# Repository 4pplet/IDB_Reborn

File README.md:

# IDB_reborn
Reborn of the PCB for the IDB60

Made in KiCad Nightly

Originally designed by pngu.
Redigned by Mattelec.

Tested via private GB of the PCB. Might need some filing though.

Any question refer to Mattelec#9468 at Discord

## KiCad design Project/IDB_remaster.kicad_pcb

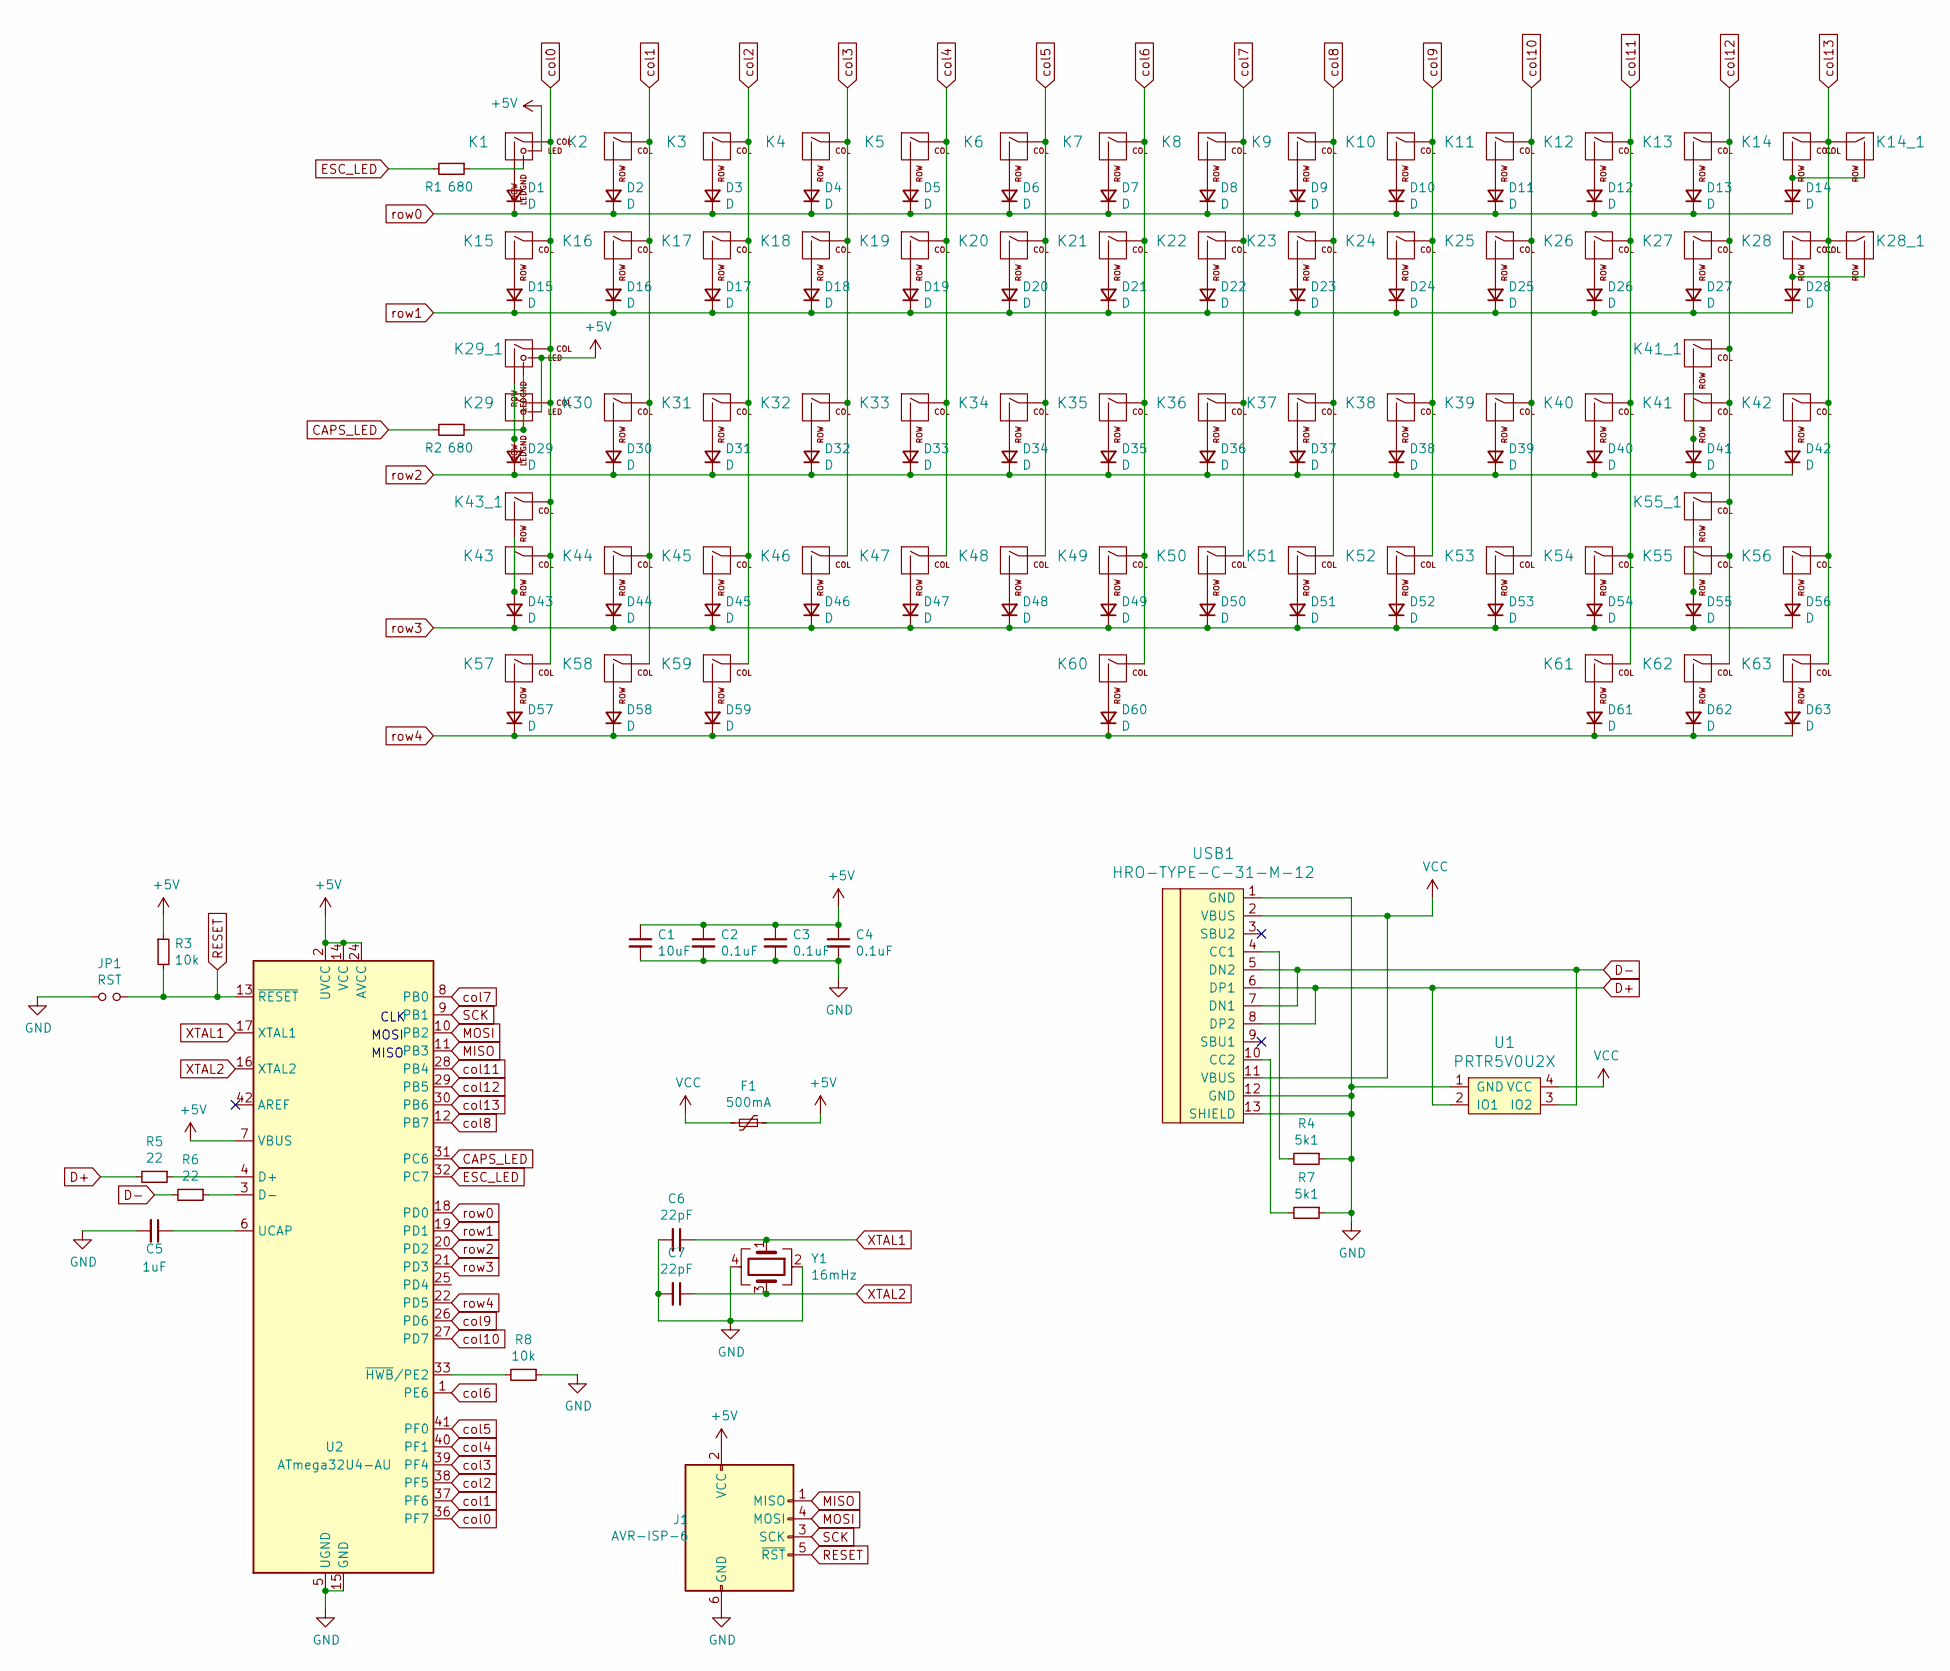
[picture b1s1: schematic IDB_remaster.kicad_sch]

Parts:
C1: 10uF; C_0805_2012Metric; LCSC C15850
C2, C3, C4: 0.1uF; C_0805_2012Metric; LCSC C49678
C5: 1uF; C_0805_2012Metric; LCSC C28323
C6, C7: 22pF; C_0805_2012Metric; LCSC C1804
D1, D2, D3, D4, D5, D6, D7, D8, D9, D10, D11, D12, D13, D14, D15, D16, D17, D18, D19, D20, D21, D22, D23, D24, D25, D26, D27, D28, D29, D30, D31, D32, D33, D34, D35, D36, D37, D38, D39, D40, D41, D42, D43, D44, D45, D46, D47, D48, D49, D50, D51, D52, D53, D54, D55, D56, D57, D58, D59, D60, D61, D62, D63: D; D_SOD-123-Pretty; LCSC C64898
F1: 500mA; Fuse_1206_3216Metric; LCSC C70076
J1: AVR-ISP-6; Reset_Pretty-Mask
JP1: RST; Reset_holes
K1: MXOnly-1U-19mm
K2, K3, K4, K5, K6, K7, K8, K9, K10, K11, K12, K13, K14_1, K16, K17, K18, K19, K20, K21, K22, K23, K24, K25, K26, K27, K30, K31, K32, K33, K34, K35, K36, K37, K38, K39, K40, K41, K42, K44, K45, K46, K47, K48, K49, K50, K51, K52, K53, K54, K56, K58, K62: MXOnly-1U-NoLED-19mm
K14: MXOnly-2U-NoLED-19mm
K15, K28, K57, K59, K61, K63: MXOnly-1.5U--NoLED19mm
K28_1: MXOnly-ISO-ROTATED-NoLED-19mm
K29: MXOnly-1.75U-19mm
K29_1: MXOnly-1.25U-ReverseLED19mm
K41_1, K43_1: MXOnly-2.25U-NoLED-19mm
K43: MXOnly-1.25U-NoLED-19mm
K55: MXOnly-1.75U-NoLED-19mm
K55_1: MXOnly-2.75U-NoLED-19mm
K60: MXOnly-7U-ReversedStabilizers-NoLED-19mm
R1, R2: 680; R_0805_2012Metric; LCSC C25324
R3, R8: 10k; R_0805_2012Metric; LCSC C17414
R4, R7: 5k1; R_0805_2012Metric; LCSC C118848
R5, R6: 22; R_0805_2012Metric; LCSC C416086
U1: PRTR5V0U2X; SOT143B; LCSC C78442
U2: ATmega32U4-AU; TQFP-44_10x10mm_P0.8mm; LCSC C44854
USB1: HRO-TYPE-C-31-M-12; HRO-TYPE-C-31-M-12-Assembly; LCSC C165948
Y1: 16mHz; Crystal_SMD_3225-4Pin_3.2x2.5mm; LCSC C13738

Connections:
+5V: C1.1, C2.1, C3.1, C4.1, F1.1, J1.2 (VCC), K1.3 (LED), K29.3 (LED), K29_1.3 (LED), R3.1, U2.2 (UVCC), U2.7 (VBUS), U2.14 (VCC), U2.24 (AVCC), U2.34 (VCC), U2.44 (AVCC)
CAPS_LED: R2.2, U2.31 (PC6)
D+: R5.2, U1.2 (IO1), USB1.6 (DP1), USB1.8 (DP2)
D-: R6.2, U1.3 (IO2), USB1.5 (DN2), USB1.7 (DN1)
ESC_LED: R1.2, U2.32 (PC7)
GND: C1.2, C2.2, C3.2, C4.2, C5.2, C6.2, C7.2, J1.6 (GND), JP1.1, R4.1, R7.1, R8.1, U1.1 (GND), U2.5 (UGND), U2.15 (GND), U2.23 (GND), U2.35 (GND), U2.43 (GND), USB1.1 (GND), USB1.12 (GND), USB1.13 (SHIELD), Y1.2, Y1.4; also elsewhere on the board
MISO: J1.1 (MISO), U2.11 (PB3)
MOSI: J1.4 (MOSI), U2.10 (PB2)
unnamed: C5.1, U2.6 (UCAP)
unnamed: D1.2 (A), K1.2 (ROW)
unnamed: D2.2 (A), K2.2 (ROW)
unnamed: D3.2 (A), K3.2 (ROW)
unnamed: D4.2 (A), K4.2 (ROW)
unnamed: D5.2 (A), K5.2 (ROW)
unnamed: D6.2 (A), K6.2 (ROW)
unnamed: D7.2 (A), K7.2 (ROW)
unnamed: D8.2 (A), K8.2 (ROW)
unnamed: D9.2 (A), K9.2 (ROW)
unnamed: D10.2 (A), K10.2 (ROW)
unnamed: D11.2 (A), K11.2 (ROW)
unnamed: D12.2 (A), K12.2 (ROW)
unnamed: D13.2 (A), K13.2 (ROW)
unnamed: D14.2 (A), K14.2 (ROW), K14_1.2 (ROW)
unnamed: D15.2 (A), K15.2 (ROW)
unnamed: D16.2 (A), K16.2 (ROW)
unnamed: D17.2 (A), K17.2 (ROW)
unnamed: D18.2 (A), K18.2 (ROW)
unnamed: D19.2 (A), K19.2 (ROW)
unnamed: D20.2 (A), K20.2 (ROW)
unnamed: D21.2 (A), K21.2 (ROW)
unnamed: D22.2 (A), K22.2 (ROW)
unnamed: D23.2 (A), K23.2 (ROW)
unnamed: D24.2 (A), K24.2 (ROW)
unnamed: D25.2 (A), K25.2 (ROW)
unnamed: D26.2 (A), K26.2 (ROW)
unnamed: D27.2 (A), K27.2 (ROW)
unnamed: D28.2 (A), K28.2 (ROW), K28_1.2 (ROW)
unnamed: D29.2 (A), K29.2 (ROW), K29_1.2 (ROW)
unnamed: D30.2 (A), K30.2 (ROW)
unnamed: D31.2 (A), K31.2 (ROW)
unnamed: D32.2 (A), K32.2 (ROW)
unnamed: D33.2 (A), K33.2 (ROW)
unnamed: D34.2 (A), K34.2 (ROW)
unnamed: D35.2 (A), K35.2 (ROW)
unnamed: D36.2 (A), K36.2 (ROW)
unnamed: D37.2 (A), K37.2 (ROW)
unnamed: D38.2 (A), K38.2 (ROW)
unnamed: D39.2 (A), K39.2 (ROW)
unnamed: D40.2 (A), K40.2 (ROW)
unnamed: D41.2 (A), K41.2 (ROW), K41_1.2 (ROW)
unnamed: D42.2 (A), K42.2 (ROW)
unnamed: D43.2 (A), K43.2 (ROW), K43_1.2 (ROW)
unnamed: D44.2 (A), K44.2 (ROW)
unnamed: D45.2 (A), K45.2 (ROW)
unnamed: D46.2 (A), K46.2 (ROW)
unnamed: D47.2 (A), K47.2 (ROW)
unnamed: D48.2 (A), K48.2 (ROW)
unnamed: D49.2 (A), K49.2 (ROW)
unnamed: D50.2 (A), K50.2 (ROW)
unnamed: D51.2 (A), K51.2 (ROW)
unnamed: D52.2 (A), K52.2 (ROW)
unnamed: D53.2 (A), K53.2 (ROW)
unnamed: D54.2 (A), K54.2 (ROW)
unnamed: D55.2 (A), K55.2 (ROW), K55_1.2 (ROW)
unnamed: D56.2 (A), K56.2 (ROW)
unnamed: D57.2 (A), K57.2 (ROW)
unnamed: D58.2 (A), K58.2 (ROW)
unnamed: D59.2 (A), K59.2 (ROW)
unnamed: D60.2 (A), K60.2 (ROW)
unnamed: D61.2 (A), K61.2 (ROW)
unnamed: D62.2 (A), K62.2 (ROW)
unnamed: D63.2 (A), K63.2 (ROW)
unnamed: K1.4 (LEDGND), R1.1
unnamed: K29.4 (LEDGND), K29_1.4 (LEDGND), R2.1
unnamed: R4.2, USB1.4 (CC1)
unnamed: R5.1, U2.4 (D+)
unnamed: R6.1, U2.3 (D-)
unnamed: R7.2, USB1.10 (CC2)
unnamed: R8.2, U2.33 (~HWB/PE2)
RESET: J1.5 (~RST), JP1.2, R3.2, U2.13 (~RESET); also elsewhere on the board
SCK: J1.3 (SCK), U2.9 (PB1)
VCC: F1.2, U1.4 (VCC), USB1.2 (VBUS), USB1.11 (VBUS)
XTAL1: C6.1, U2.17 (XTAL1), Y1.1
XTAL2: C7.1, U2.16 (XTAL2), Y1.3
col0: K1.1 (COL), K15.1 (COL), K29.1 (COL), K29_1.1 (COL), K43.1 (COL), K43_1.1 (COL), K57.1 (COL), U2.36 (PF7)
col1: K2.1 (COL), K16.1 (COL), K30.1 (COL), K44.1 (COL), K58.1 (COL), U2.37 (PF6)
col2: K3.1 (COL), K17.1 (COL), K31.1 (COL), K45.1 (COL), K59.1 (COL), U2.38 (PF5)
col3: K4.1 (COL), K18.1 (COL), K32.1 (COL), K46.1 (COL), U2.39 (PF4)
col4: K5.1 (COL), K19.1 (COL), K33.1 (COL), K47.1 (COL), U2.40 (PF1)
col5: K6.1 (COL), K20.1 (COL), K34.1 (COL), K48.1 (COL), U2.41 (PF0)
col6: K7.1 (COL), K21.1 (COL), K35.1 (COL), K49.1 (COL), K60.1 (COL), U2.1 (PE6)
col7: K8.1 (COL), K22.1 (COL), K36.1 (COL), K50.1 (COL), U2.8 (PB0)
col8: K9.1 (COL), K23.1 (COL), K37.1 (COL), K51.1 (COL), U2.12 (PB7)
col9: K10.1 (COL), K24.1 (COL), K38.1 (COL), K52.1 (COL), U2.26 (PD6)
col10: K11.1 (COL), K25.1 (COL), K39.1 (COL), K53.1 (COL), U2.27 (PD7)
col11: K12.1 (COL), K26.1 (COL), K40.1 (COL), K54.1 (COL), K61.1 (COL), U2.28 (PB4)
col12: K13.1 (COL), K27.1 (COL), K41.1 (COL), K41_1.1 (COL), K55.1 (COL), K55_1.1 (COL), K62.1 (COL), U2.29 (PB5)
col13: K14.1 (COL), K14_1.1 (COL), K28.1 (COL), K28_1.1 (COL), K42.1 (COL), K56.1 (COL), K63.1 (COL), U2.30 (PB6)
row0: D1.1 (K), D2.1 (K), D3.1 (K), D4.1 (K), D5.1 (K), D6.1 (K), D7.1 (K), D8.1 (K), D9.1 (K), D10.1 (K), D11.1 (K), D12.1 (K), D13.1 (K), D14.1 (K), U2.18 (PD0)
row1: D15.1 (K), D16.1 (K), D17.1 (K), D18.1 (K), D19.1 (K), D20.1 (K), D21.1 (K), D22.1 (K), D23.1 (K), D24.1 (K), D25.1 (K), D26.1 (K), D27.1 (K), D28.1 (K), U2.19 (PD1)
row2: D29.1 (K), D30.1 (K), D31.1 (K), D32.1 (K), D33.1 (K), D34.1 (K), D35.1 (K), D36.1 (K), D37.1 (K), D38.1 (K), D39.1 (K), D40.1 (K), D41.1 (K), D42.1 (K), U2.20 (PD2)
row3: D43.1 (K), D44.1 (K), D45.1 (K), D46.1 (K), D47.1 (K), D48.1 (K), D49.1 (K), D50.1 (K), D51.1 (K), D52.1 (K), D53.1 (K), D54.1 (K), D55.1 (K), D56.1 (K), U2.21 (PD3)
row4: D57.1 (K), D58.1 (K), D59.1 (K), D60.1 (K), D61.1 (K), D62.1 (K), D63.1 (K), U2.22 (PD5)

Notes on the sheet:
MOSI
MISO
CLK

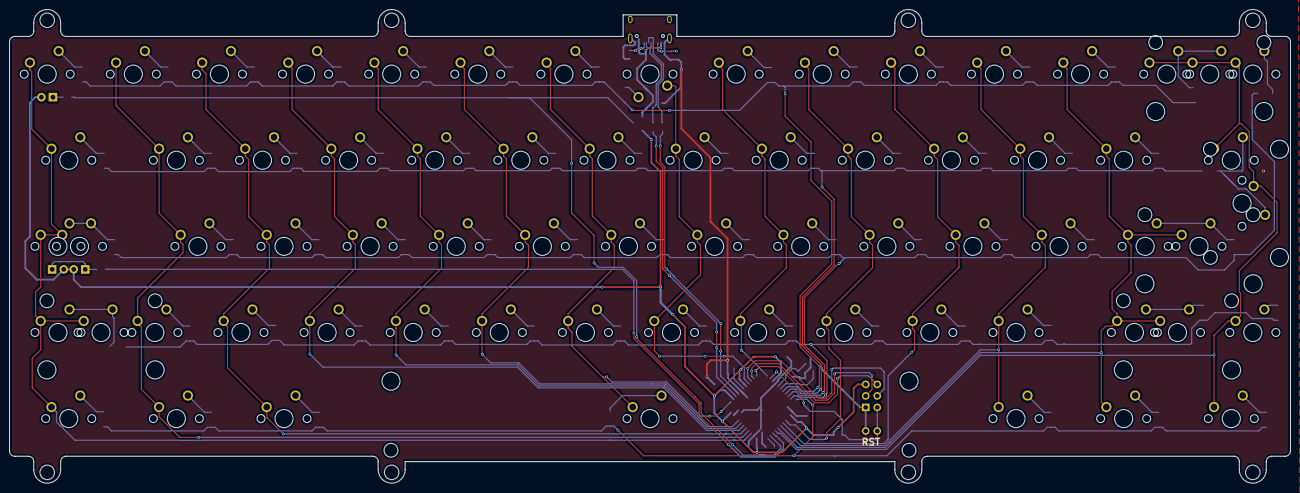
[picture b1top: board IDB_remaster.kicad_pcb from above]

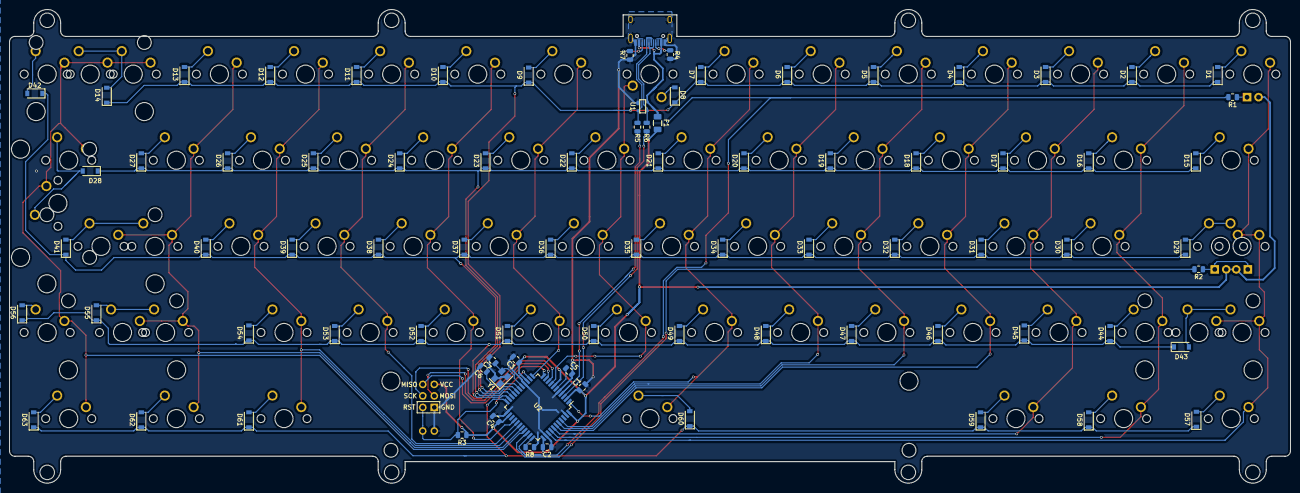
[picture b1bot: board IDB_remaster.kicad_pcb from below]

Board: 2 copper layers, 282.6 x 104.5 mm, 154 parts (84 on the bottom side), 103 nets.

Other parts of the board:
RST: JP1; Reset_holes

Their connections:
GND: RST.1; also elsewhere on the board
RESET: RST.2; also elsewhere on the board

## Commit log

2021-07-06 V1.0
    The start
2021-07-06 V1.0.1
2021-07-11 V1.2
    Pics
2021-10-23 V1.3
2021-10-23 V1.3.1
2021-10-23 Final
2021-10-23 Added Gerber files
